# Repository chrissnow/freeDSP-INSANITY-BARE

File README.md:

# freeDSP INSANITY BARE

BOARD STATUS: WORK IN PROGRESS - DO NOT BUILD!

MAIN COORDINATOR: [sudlud](https://github.com/sudlud), [blauespferd](https://github.com/blauespferd)

Working directory for the modularized freeDSP INSANITY (the big brother of freeDSP classic). (Final board-name still undefined)

LIBRARY:

This project uses the freeDSP-KiCad-Library:
https://github.com/freeDSP/freeDSP-KiCadLibrary.git

The library is included as a submodule. It can be initialized using the following commands:

git submodule init

git submodule update

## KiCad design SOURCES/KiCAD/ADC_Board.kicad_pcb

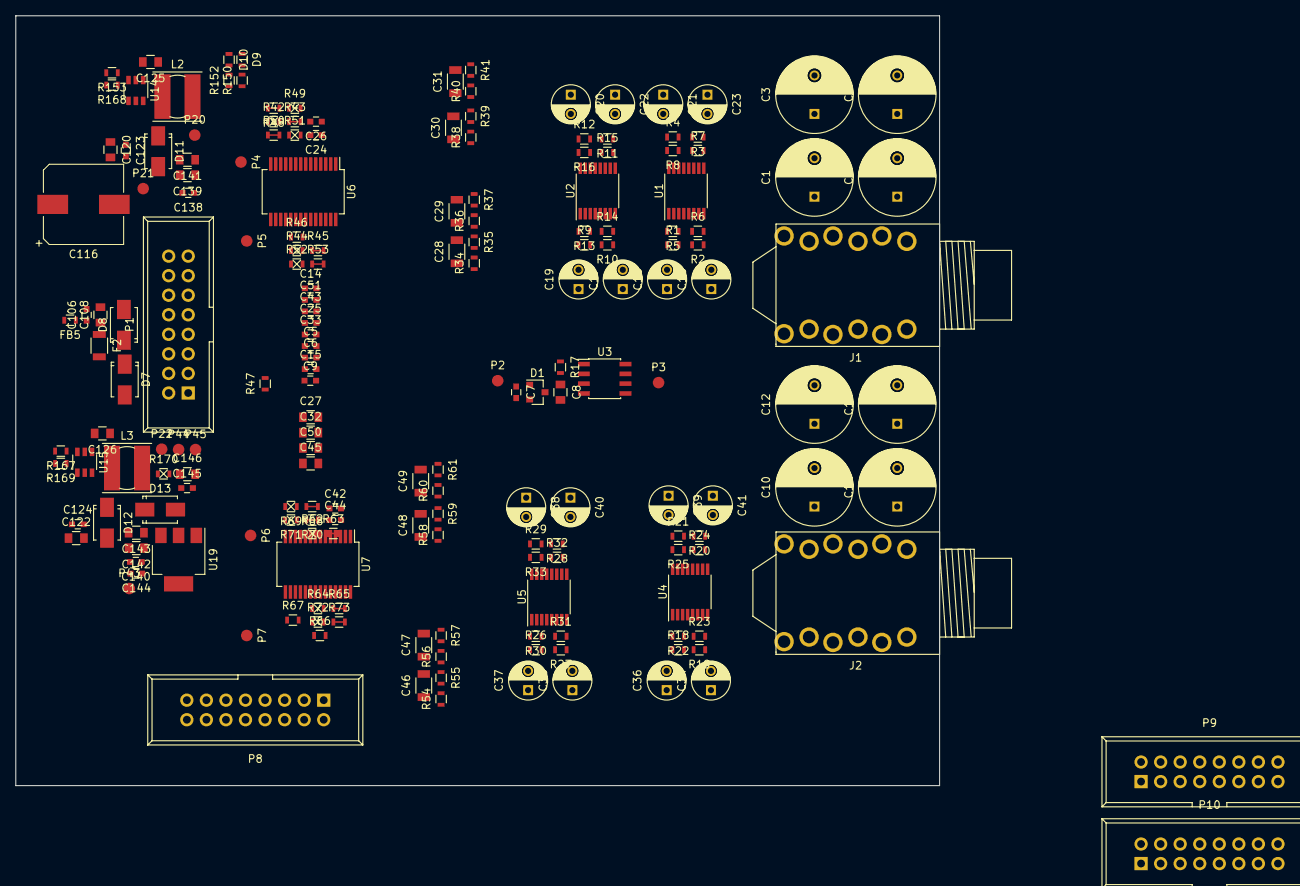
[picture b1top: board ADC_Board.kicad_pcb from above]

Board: 2 copper layers, 120.0 x 100.0 mm, 189 parts (0 on the bottom side), 122 nets, no tracks yet.

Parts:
C1, C2, C3, C4, C10, C11, C12, C13: 22u; C_Radial_D10_L16_P5
C5, C6, C7, C9, C14, C15, C25, C26, C33, C43, C44, C51, C106, C123, C124, C138, C140, C144, C145: 100n; C_0603
C8, C27, C32, C45, C50, C108, C120, C122, C139, C141, C142, C143, C146: 10u; C_0805
C16, C17, C18, C19, C20, C21, C22, C23, C34, C35, C36, C37, C38, C39, C40, C41: 10u; C_Radial_D5_L11_P2.5
C24, C42: 1u; C_0603
C28, C29, C30, C31, C46, C47, C48, C49: 1.5n; C_1206
C116: 100u; CP_Elec_10x10.5
C125, C126: 150n; C_0805
D1: LM4040DYM3-2.5; SOT-23
D7, D11, D12, D13: B150; SMA
D8: SMAJ28A; SMA
D9, D10: green; R_0603
F2: 0ZCJ0050AF2E; R_1206
FB5: BLM18PG471SN1; R_0603
J1, J2: AUDIO_JACK_STEREO_12PIN_FCR1117
L2, L3: 47u; Choke_SMD_6.0x5.8
P1, P8, P9, P10: STDCONN; IDC_Header_Straight_16pins
P2, P3, P4, P5, P6, P7, P20, P21, P22, P43, P44, P45: TST; Measurement_Point_Round-SMD-Pad_Small
R1, R2, R3, R4, R17, R18, R19, R20, R21, R46, R66: 10k; R_0603
R5, R6, R7, R8, R22, R23, R24, R25: 8.06k; R_0603
R9, R10, R11, R12, R13, R14, R15, R16, R26, R27, R28, R29, R30, R31, R32, R33: 4.7k; R_0603
R34, R35, R36, R37, R38, R39, R40, R41, R54, R55, R56, R57, R58, R59, R60, R61: 330; R_0603
R42, R44, R49, R51, R52, R62, R64, R69, R71, R72, R170: Jumper_NO_Small; R_0603_Solderjumper_Open
R43, R45, R48, R50, R53, R63, R65, R68, R70, R73: Jumper_NC_Small; R_0603_Solderjumper_Closed
R47, R67: 33; R_0603
R150, R152: 1k; R_0603
R153, R167: 1.02k; R_0603
R168: 3.4k; R_0603
R169: 5.62k; R_0603
U1, U2, U4, U5: OPA4353; TSSOP-16_4.4x5mm_Pitch0.65mm
U3: OPA337; SOIC-8_3.9x4.9mm_Pitch1.27mm
U6, U7: AK5384; SSOP-28_5.3x10.2mm_Pitch0.65mm
U14, U15: LM2842Y; SOT23-6_1.7x3.0mm_Pitch0.95mm
U19: LD1117DT50TR; SOT-223

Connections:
+3V3: C138.1, C139.1, C141.1, L2.2, P20.1, R150.1, R168.2
+5V: C5.1, C6.1, C9.1, C14.1, C15.1, C25.1, C27.1, C32.1, C33.1, C43.1, C45.1, C50.1, C51.1, C145.1, C146.1, D13.2, P44.1, R17.1, R42.1, R44.1, R46.1, R48.2, R50.1, R52.1, R62.1, R64.1, R66.1, R68.1, R70.1, R72.1, R152.1, R170.2, U1.4, U2.4, U3.7, U4.4, U5.4, U6.8, U6.19, U6.20, U7.8, U7.19, U7.20, U19.2
ADC1+: C19.2, R13.2, U2.1
ADC1-: C18.2, R5.2, R9.1, U1.1
ADC2+: C17.2, R14.2, U2.7
ADC2-: C16.2, R6.2, R10.1, U1.7
ADC3+: C22.2, R15.2, U2.10
ADC3-: C23.2, R7.2, R11.1, U1.10
ADC4+: C20.2, R16.2, U2.16
ADC4-: C21.2, R8.2, R12.1, U1.16
ADC5+: C37.2, R30.2, U5.1
ADC5-: C36.2, R22.2, R26.1, U4.1
ADC6+: C35.2, R31.2, U5.7
ADC6-: C34.2, R23.2, R27.1, U4.7
ADC7+: C40.2, R32.2, U5.10
ADC7-: C41.2, R24.2, R28.1, U4.10
ADC8+: C38.2, R33.2, U5.16
ADC8-: C39.2, R25.2, R29.1, U4.16
BCLK_IN3: P1.7, P8.7, P9.7, P10.7, U6.16, U7.16
GND: C5.2, C6.2, C7.2, C8.2, C9.2, C14.2, C15.2, C24.2, C25.2, C26.2, C27.2, C32.2, C33.2, C42.2, C43.2, C44.2, C45.2, C50.2, C51.2, C106.2, C108.2, C116.2, C120.2, C122.2, C123.2, C124.2, C138.2, C139.2, C140.2, C141.2, C142.2, C143.2, C144.2, C145.2, C146.2, D1.2, D8.2, D9.1, D10.1, D11.2, D12.2, J1.1, J1.2, J1.3, J1.4, J1.7, J1.8, J1.9, J1.10, J2.1, J2.2, J2.3, J2.4, J2.7, J2.8, J2.9, J2.10, P1.2, P1.4, P1.6, P1.8, P1.10, P1.12, P1.14, P1.16, P8.2, P8.4, P8.6, P8.8, P8.10, P8.12, P8.14, P8.16, P9.2, P9.4, P9.6, P9.8, P9.10, P9.12, P9.14, P9.16, P10.2, P10.4, P10.6, P10.8, P10.10, P10.12, P10.14, P10.16, P21.1, P43.1, P45.1, R43.2, R45.2, R49.2, R51.2, R53.2, R63.2, R65.2, R69.2, R71.2, R73.2, R153.2, R167.2, U1.13, U2.13, U3.4, U4.13, U5.13, U6.5, U6.7, U6.12, U6.21, U7.5, U7.7, U7.21, U14.2, U15.2, U19.1
IN1: C1.1, J1.6
IN2: C2.1, J1.5
IN3: C3.1, J1.12
IN4: C4.1, J1.11
IN5: C10.1, J2.6
IN6: C11.1, J2.5
IN7: C12.1, J2.12
IN8: C13.1, J2.11
LRCLK_IN3\MP13: P1.9, P8.9, P9.9, P10.9, U6.15, U7.15
MCLK_ADC0: P1.15, P9.15, U6.13
MCLK_ADC1: P8.15, P10.15, U7.13
unnamed: C1.2, R1.1
unnamed: C2.2, R2.1
unnamed: C3.2, R3.1
unnamed: C4.2, R4.1
unnamed: C7.1, C8.1, D1.1, P2.1, R17.2, U3.3
unnamed: C10.2, R18.1
unnamed: C11.2, R19.1
unnamed: C12.2, R20.1
unnamed: C13.2, R21.1
unnamed: C16.1, R34.2
unnamed: C17.1, R35.2
unnamed: C18.1, R36.2
unnamed: C19.1, R37.2
unnamed: C20.1, R38.2
unnamed: C21.1, R39.2
unnamed: C22.1, R40.2
unnamed: C23.1, R41.2
unnamed: C24.1, C26.1, U6.6
unnamed: C28.1, R34.1, U6.25
unnamed: C28.2, R35.1, U6.26
unnamed: C29.1, R36.1, U6.27
unnamed: C29.2, R37.1, U6.28
unnamed: C30.1, R38.1, U6.1
unnamed: C30.2, R39.1, U6.2
unnamed: C31.1, R40.1, U6.3
unnamed: C31.2, R41.1, U6.4
unnamed: C34.1, R54.2
unnamed: C35.1, R55.2
unnamed: C36.1, R56.2
unnamed: C37.1, R57.2
unnamed: C38.1, R58.2
unnamed: C39.1, R59.2
unnamed: C40.1, R60.2
unnamed: C41.1, R61.2
unnamed: C42.1, C44.1, U7.6
unnamed: C46.1, R54.1, U7.25
unnamed: C46.2, R55.1, U7.26
unnamed: C47.1, R56.1, U7.27
unnamed: C47.2, R57.1, U7.28
unnamed: C48.1, R58.1, U7.1
unnamed: C48.2, R59.1, U7.2
unnamed: C49.1, R60.1, U7.3
unnamed: C49.2, R61.1, U7.4
unnamed: C106.1, C108.1, D8.1, F2.1, FB5.1
unnamed: C116.1, C120.1, C122.1, C123.1, C124.1, FB5.2, U14.4, U14.5, U15.4, U15.5
unnamed: C125.1, D11.1, L2.1, U14.6
unnamed: C125.2, U14.1
unnamed: C126.1, D12.1, L3.1, U15.6
unnamed: C126.2, U15.1
unnamed: C140.1, C142.1, C143.1, C144.1, D13.1, L3.2, P22.1, R169.2, R170.1, U19.3
unnamed: D7.1, F2.2
unnamed: D9.2, R150.2
unnamed: D10.2, R152.2
unnamed: P4.1, U6.14
unnamed: P5.1, R46.2, U6.22
unnamed: P6.1, U7.14
unnamed: P7.1, R66.2, U7.22
unnamed: R1.2, R5.1, U1.2
unnamed: R2.2, R6.1, U1.6
unnamed: R3.2, R7.1, U1.11
unnamed: R4.2, R8.1, U1.15
unnamed: R10.2, R14.1, U2.6
unnamed: R11.2, R15.1, U2.11
unnamed: R12.2, R16.1, U2.15
unnamed: R9.2, R13.1, U2.2
unnamed: R18.2, R22.1, U4.2
unnamed: R19.2, R23.1, U4.6
unnamed: R20.2, R24.1, U4.11
unnamed: R21.2, R25.1, U4.15
unnamed: R26.2, R30.1, U5.2
unnamed: R27.2, R31.1, U5.6
unnamed: R28.2, R32.1, U5.11
unnamed: R29.2, R33.1, U5.15
unnamed: R42.2, R43.1, U6.10
unnamed: R44.2, R45.1, U6.23
unnamed: R47.2, U6.17
unnamed: R48.1, R49.1, U6.9
unnamed: R50.2, R51.1, U6.11
unnamed: R52.2, R53.1, U6.24
unnamed: R62.2, R63.1, U7.10
unnamed: R64.2, R65.1, U7.23
unnamed: R67.2, U7.18
unnamed: R68.2, R69.1, U7.9
unnamed: R70.2, R71.1, U7.11
unnamed: R72.2, R73.1, U7.24
unnamed: R153.1, R168.1, U14.3
unnamed: R167.1, R169.1, U15.3
SDATA_IN3: P8.5, P10.5, R67.1
TDM_OUT: R47.1, U7.12
VIN: D7.2, P1.1, P8.1, P9.1, P10.1
VREF_ADC: P3.1, U1.3, U1.5, U1.12, U1.14, U2.3, U2.5, U2.12, U2.14, U3.2, U3.6, U4.3, U4.5, U4.12, U4.14, U5.3, U5.5, U5.12, U5.14

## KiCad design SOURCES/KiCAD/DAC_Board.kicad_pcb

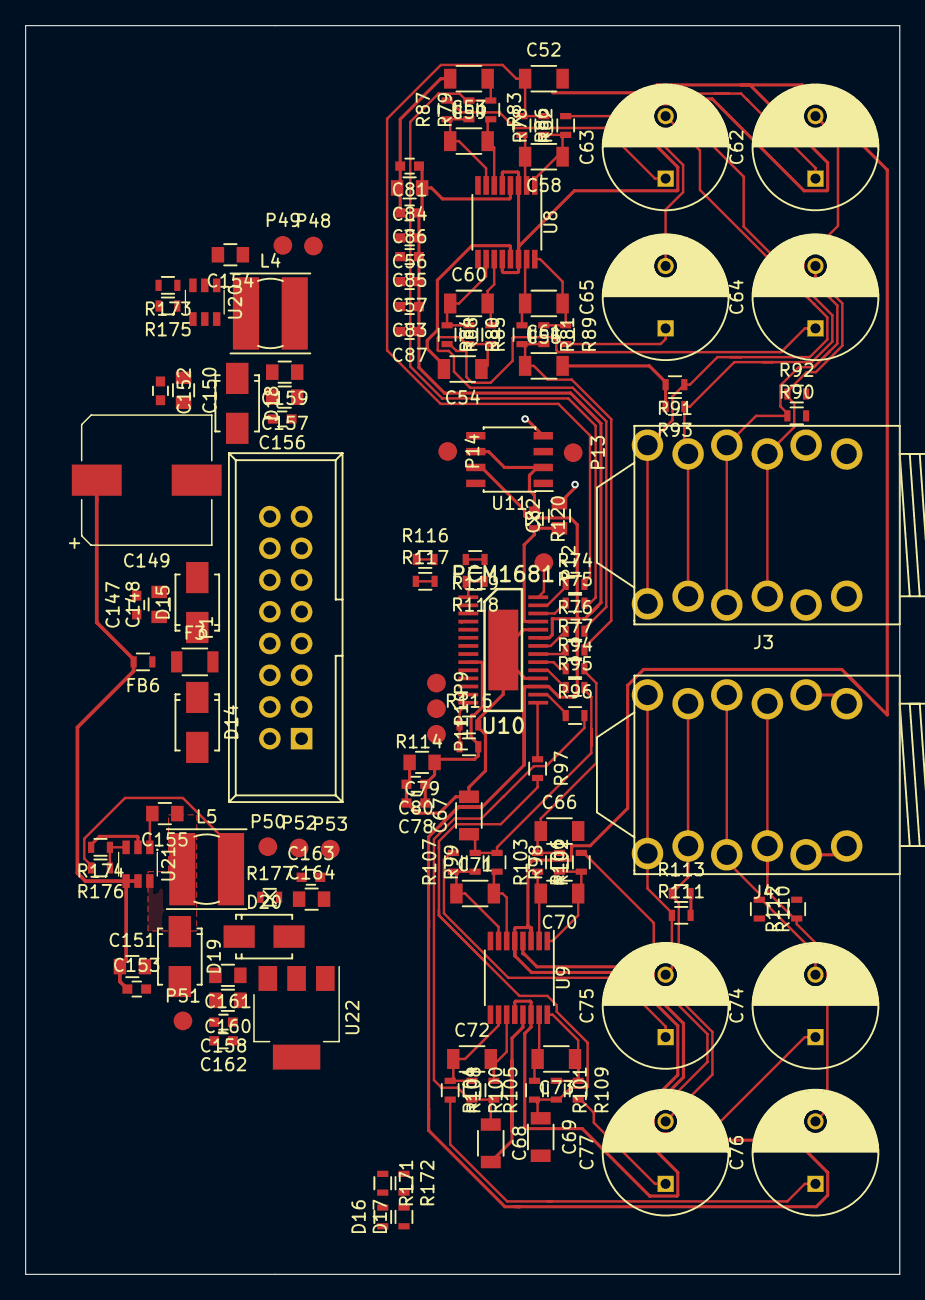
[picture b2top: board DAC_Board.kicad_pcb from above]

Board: 2 copper layers, 70.0 x 100.0 mm, 141 parts (0 on the bottom side), 79 nets.

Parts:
C52, C53, C54, C55, C66, C67, C68, C69: 4700p; C_1206
C56, C57, C78, C85, C86, C87, C147, C152, C153, C156, C158, C162, C163: 100n; C_0603
C58, C59, C60, C61, C70, C71, C72, C73: 470p; C_1206
C62, C63, C64, C65, C74, C75, C76, C77: 10u; C_Radial_D10_L16_P5
C79, C82, C84, C148, C150, C151, C157, C159, C160, C161, C164: 10u; C_0805
C80, C81, C83: 1u; C_0603
C149: 100u; CP_Elec_10x10.5
C154, C155: 150n; C_0805
D14, D18, D19, D20: B150; SMA
D15: SMAJ28A; SMA
D16, D17: green; R_0603
F3: 0ZCJ0050AF2E; R_1206
FB6: BLM18PG471SN1; R_0603
J3, J4: AUDIO_JACK_STEREO_12PIN_FCR1117
L4, L5: 47u; Choke_SMD_6.0x5.8
P1: STDCONN; IDC_Header_Straight_16pins
P9, P10, P11, P12, P13, P14, P48, P49, P50, P51, P52, P53: TST; Measurement_Point_Round-SMD-Pad_Small
R74, R75, R76, R77, R94, R95, R96, R97: 6.2k; R_0603
R78, R79, R80, R81, R98, R99, R100, R101: 5.9k; R_0603
R82, R83, R84, R85, R102, R103, R104, R105: 430; R_0603
R86, R87, R88, R89, R106, R107, R108, R109: 47; R_0603
R90, R91, R92, R93, R110, R111, R112, R113: 10k; R_0603
R114, R115: 220k; R_0603
R116, R117, R118, R119: Jumper_NC_Small; R_0603_Solderjumper_Closed
R120, R177: Jumper_NO_Small; R_0603_Solderjumper_Open
R171, R172: 1k; R_0603
R173, R174: 1.02k; R_0603
R175: 3.4k; R_0603
R176: 5.62k; R_0603
U8, U9: OPA4353; TSSOP-16_4.4x5mm_Pitch0.65mm
U10: PCM1681; TSSOP-28_10x5mm_Pitch0.65mm_PCM1681
U11: OPA337; SOIC-8_3.9x4.9mm_Pitch1.27mm
U20, U21: LM2842Y; SOT23-6_1.7x3.0mm_Pitch0.95mm
U22: LD1117DT50TR; SOT-223

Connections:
+3V3: C78.1, C79.1, C80.1, C156.1, C157.1, C159.1, L4.2, P48.1, R114.1, R118.1, R119.1, R171.1, R175.2, U10.9
+5V: C56.1, C57.1, C81.1, C83.1, C84.1, C85.1, C86.1, C87.1, C163.1, C164.1, D20.2, P52.1, R172.1, R177.2, U8.4, U9.4, U10.17, U10.23, U11.7, U22.2
/DAC/BCLK_OUT3: P1.7, U10.7
/DAC/LRCLK_OUT3: P1.9, U10.8
/DAC/MCLK_DAC: P1.15, U10.5
/DAC/SDATA_OUT3: P1.3, U10.6
DAC1: R74.1, U10.27
DAC1_OUT: C62.2, J3.8, J3.11, R90.1
DAC2: R75.1, U10.26
DAC2_OUT: C63.2, J3.9, J3.12, R91.1
DAC3: R76.1, U10.22
DAC3_OUT: C64.2, J3.2, J3.5, R92.1
DAC4: R77.1, U10.21
DAC4_OUT: C65.2, J3.3, J3.6, R93.1
DAC5: R94.1, U10.20
DAC5_OUT: C74.2, J4.8, J4.11, R110.1
DAC6: R95.1, U10.19
DAC6_OUT: C75.2, J4.9, J4.12, R111.1
DAC7: R96.1, U10.16
DAC7_OUT: C76.2, J4.2, J4.5, R112.1
DAC8: R97.1, U10.15
DAC8_OUT: C77.2, J4.3, J4.6, R113.1
GND: C52.2, C53.2, C54.2, C55.2, C56.2, C57.2, C66.2, C67.2, C68.2, C69.2, C78.2, C79.2, C80.2, C81.2, C82.2, C83.2, C84.2, C85.2, C86.2, C87.2, C147.2, C148.2, C149.2, C150.2, C151.2, C152.2, C153.2, C156.2, C157.2, C158.2, C159.2, C160.2, C161.2, C162.2, C163.2, C164.2, D15.2, D16.1, D17.1, D18.2, D19.2, J3.1, J3.4, J3.7, J3.10, J4.1, J4.4, J4.7, J4.10, P1.2, P1.4, P1.6, P1.8, P1.10, P1.12, P1.14, P1.16, P49.1, P51.1, P53.1, R90.2, R91.2, R92.2, R93.2, R110.2, R111.2, R112.2, R113.2, R115.2, R116.1, R117.1, R173.2, R174.2, U8.13, U9.13, U10.10, U10.18, U10.24, U10.29, U11.4, U20.2, U21.2, U22.1
unnamed: C52.1, R74.2, R78.2, R82.1
unnamed: C53.1, R75.2, R79.2, R83.1
unnamed: C54.1, R76.2, R80.2, R84.1
unnamed: C55.1, R77.2, R81.2, R85.1
unnamed: C58.1, R78.1, R86.1, U8.1
unnamed: C58.2, R82.2, U8.2
unnamed: C59.1, R79.1, R87.1, U8.7
unnamed: C59.2, R83.2, U8.6
unnamed: C60.1, R80.1, R88.1, U8.10
unnamed: C60.2, R84.2, U8.11
unnamed: C61.1, R81.1, R89.1, U8.16
unnamed: C61.2, R85.2, U8.15
unnamed: C62.1, R86.2
unnamed: C63.1, R87.2
unnamed: C64.1, R88.2
unnamed: C65.1, R89.2
unnamed: C66.1, R94.2, R98.2, R102.1
unnamed: C67.1, R95.2, R99.2, R103.1
unnamed: C68.1, R96.2, R100.2, R104.1
unnamed: C69.1, R97.2, R101.2, R105.1
unnamed: C70.1, R98.1, R106.1, U9.1
unnamed: C70.2, R102.2, U9.2
unnamed: C71.1, R99.1, R107.1, U9.7
unnamed: C71.2, R103.2, U9.6
unnamed: C72.1, R100.1, R108.1, U9.10
unnamed: C72.2, R104.2, U9.11
unnamed: C73.1, R101.1, R109.1, U9.16
unnamed: C73.2, R105.2, U9.15
unnamed: C74.1, R106.2
unnamed: C75.1, R107.2
unnamed: C76.1, R108.2
unnamed: C77.1, R109.2
unnamed: C82.1, P13.1, R120.2, U10.25, U11.3
unnamed: C147.1, C148.1, D15.1, F3.1, FB6.1
unnamed: C149.1, C150.1, C151.1, C152.1, C153.1, FB6.2, U20.4, U20.5, U21.4, U21.5
unnamed: C154.1, D18.1, L4.1, U20.6
unnamed: C154.2, U20.1
unnamed: C155.1, D19.1, L5.1, U21.6
unnamed: C155.2, U21.1
unnamed: C158.1, C160.1, C161.1, C162.1, D20.1, L5.2, P50.1, R176.2, R177.1, U22.3
unnamed: D14.1, F3.2
unnamed: D16.2, R171.2
unnamed: D17.2, R172.2
unnamed: P9.1, U10.11
unnamed: P10.1, U10.12
unnamed: P11.1, U10.13
unnamed: P12.1, U10.28
unnamed: R114.2, R115.1, U10.14
unnamed: R116.2, U10.3
unnamed: R117.2, U10.4
unnamed: R118.2, U10.1
unnamed: R119.2, U10.2
unnamed: R173.1, R175.1, U20.3
unnamed: R174.1, R176.1, U21.3
VIN: D14.2, P1.1
VREF_DAC: P14.1, R120.1, U8.3, U8.5, U8.12, U8.14, U9.3, U9.5, U9.12, U9.14, U11.2, U11.6

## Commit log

2020-01-18 freeDSP-INSANITY modularized into 3 Boards
    - INSANITY modularized into 3 Boards (ADC_Board, DAC_Board, DSP_Board)
    DSP_Board:
    - removed Cinch IN/OUT for SPDIF
    - 4 Standard Connectors IN, 4 Standard Connectors OUT
    - new Clock-Buffer with 10 Outputs
    - PCB completed (untested)
